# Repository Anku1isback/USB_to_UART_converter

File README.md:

📌 Overview

This board converts USB signals from a USB Type-C connector into UART TX/RX signals for programming and debugging microcontrollers.
The design follows the CP2102N reference guidelines and includes proper USB-C configuration, ESD protection, decoupling networks, and clean PCB routing.

🧩 Features

USB Type-C (USB 2.0) input

CP2102N-Axx-QFN28 USB–UART converter

TX/RX activity LEDs

ESD protection on D+, D–, CC1, CC2

5.1 kΩ CC resistors for USB-C device mode

Differential pair routing for USB data lines

Thick traces for VBUS and GND

Multiple thermal vias under CP2102N for heat dissipation

2-layer PCB with clean layout

0 ERC and 0 DRC errors in KiCad

🛠 Hardware Components
Component	Description
CP2102N-A01-QFN28	USB–UART bridge IC
USB-C Receptacle (USB 2.0)	Input connector
R1, R2 — 5.1 kΩ	CC1/CC2 pull-downs for device mode
Low-capacitance ESD Diodes	Protection for D+, D–, CC lines
C1, C2 — 100 nF	Decoupling (VREGIN, VDD)
C3, C4 — 100 nF	VBUS filtering
LEDs (D1, D2)	TX/RX indicators
R6, R7 — 470 Ω	LED current limit
J2 Header	TX, RX, RST, GND, VBUS output
🔧 Circuit Description

The USB-C connector provides VBUS (5V), GND, and D+/D– to the CP2102N.
Two 5.1 kΩ resistors on CC1 and CC2 configure the board as a USB device, enabling power negotiation.

D+/D– are routed as a differential pair directly into the CP2102N, protected by low-capacitance ESD diodes.
The chip’s internal LDO outputs 3.3V on VDD, stabilized using 100 nF decoupling capacitors.

TX and RX pins drive activity LEDs using 470 Ω resistors, while the main UART header exposes:

TXD

RXD

RST

VBUS

GND

🖥️ PCB Layout Highlights

2-layer PCB

Clean differential routing for USB D+/D–

Thick traces for VBUS and ground connections

Thin traces for signal lines

Via-in-pad array under CP2102N for thermal relief

Short trace lengths for decoupling capacitors

Shield properly grounded for noise reduction

🧪 Project Workflow

Studied CP2102N datasheet and typical application circuit

Built schematic in KiCad

Selected capacitor/resistor values based on electrical characteristics

Added ESD protection and USB-C configuration resistors

Performed ERC checks → 0 errors

Loaded to PCB editor and routed 2-layer layout

Added thermal vias + power trace width optimization

Performed DRC checks → 0 errors

Generated Gerbers for manufacturing

📁 Repository Structure
├── schematic/          # KiCad schematic files
├── pcb/                # 2-layer PCB layout files
├── gerbers/            # Manufacturing outputs
├── images/             # Renders, plots, screenshots
└── README.md           # Project documentation

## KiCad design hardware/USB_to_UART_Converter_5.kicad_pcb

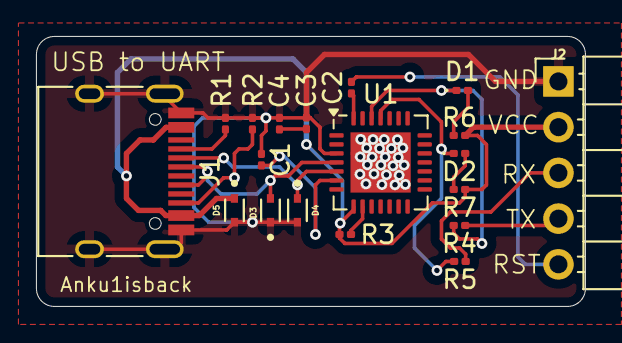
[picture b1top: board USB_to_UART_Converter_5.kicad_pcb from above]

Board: 2 copper layers, 30.5 x 15.0 mm, 19 parts (0 on the bottom side), 16 nets.

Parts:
C1, C2, C3, C4: 100nF; C_0201_0603Metric
D1, D2: LED; LED_0201_0603Metric
D3, D4, D5: LESD5D5.0CT1G; TVS_LESD5D5.0CT1G
J1: USB_C_Receptacle_USB2.0_16P; USB_C_Receptacle_HRO_TYPE-C-31-M-12
J2: Conn_01x05_Pin; PinHeader_1x05_P2.54mm_Horizontal
R1, R2: 5.1K; R_0201_0603Metric
R3: 10K; R_0201_0603Metric
R4, R5, R6, R7: 1K; R_0201_0603Metric
U1: CP2102N-Axx-xQFN28; QFN-28-1EP_5x5mm_P0.5mm_EP3.35x3.35mm

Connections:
/D+: D3.2, J1.A6 (D+), J1.B6 (D+), U1.4 (D+)
/D-: D4.1, J1.A7 (D-), J1.B7 (D-), U1.5 (D-)
/RST: C2.2, J2.5
/RX: J2.3, R5.1
/TX: J2.4, R4.1
GND: C1.1, C3.2, C4.2, D3.1, D4.2, D5.2, J1.A1 (GND), J1.A12 (GND), J1.B1 (GND), J1.B12 (GND), J1.S1 (SHIELD), J2.1, R1.2, R2.2, U1.3 (GND), U1.29 (GND)
unnamed: D1.2 (A), R6.2
unnamed: D1.1 (K), R4.2, U1.26 (TXD)
unnamed: D2.2 (A), R7.2
unnamed: D2.1 (K), R5.2, U1.25 (RXD)
unnamed: J1.A5 (CC1), R1.1
unnamed: J1.B5 (CC2), R2.1
unnamed: C1.2, U1.6 (VDD)
unnamed: C2.1, U1.28 (~DTR)
unnamed: R3.2, U1.9 (~RST)
VBUS: C3.1, C4.1, D5.1, J1.A4 (VBUS), J1.A9 (VBUS), J1.B4 (VBUS), J1.B9 (VBUS), J2.2, R3.1, R6.1, R7.1, U1.7 (VREGIN), U1.8 (VBUS)
